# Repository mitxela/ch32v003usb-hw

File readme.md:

# CH32V003 USB dev board

This is a simple and tiny USB dev board for the CH32V003 using CNLohr's ch32v003fun and rv003usb.

2 layer board, 0.8mm thickness.

The 1.5K resistor can be connected either to D5 or to VDD (not both). The series resistors on the underside are optional, cut the traces under them if you want to fit them.

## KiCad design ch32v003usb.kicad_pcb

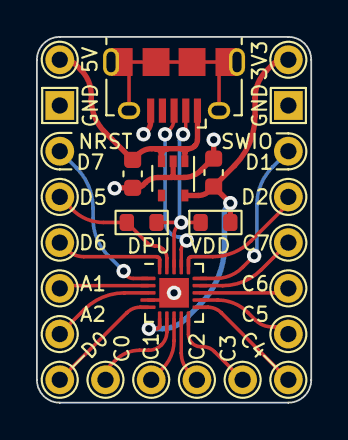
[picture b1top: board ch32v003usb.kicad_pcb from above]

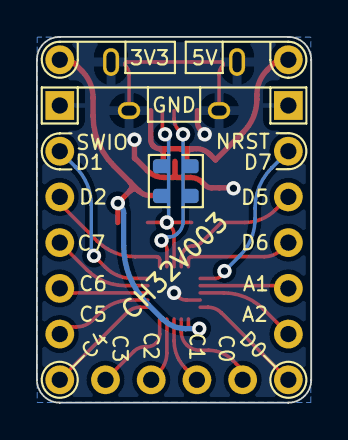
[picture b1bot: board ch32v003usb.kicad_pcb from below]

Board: 2 copper layers, 15.2 x 20.3 mm, 29 parts (2 on the bottom side), 21 nets.

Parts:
C1, C2: 1u; C_0603_1608Metric
J1: USB_B_Micro; USB_Micro-B_Amphenol_10118194_Horizontal
R1, R2: 1K5; R_0603_1608Metric
R3, R4: 33R; R_0603_1608Metric
TP1: C5; TestPoint_THTPad_D1.5mm_Drill0.7mm
TP2: D6; TestPoint_THTPad_D1.5mm_Drill0.7mm
TP3: A2; TestPoint_THTPad_D1.5mm_Drill0.7mm
TP4: D0; TestPoint_THTPad_D1.5mm_Drill0.7mm
TP5: C1; TestPoint_THTPad_D1.5mm_Drill0.7mm
TP6: 3V3; TestPoint_THTPad_D1.5mm_Drill0.7mm
TP7: C2; TestPoint_THTPad_D1.5mm_Drill0.7mm
TP8: C0; TestPoint_THTPad_D1.5mm_Drill0.7mm
TP9: C3; TestPoint_THTPad_D1.5mm_Drill0.7mm
TP10: C4; TestPoint_THTPad_D1.5mm_Drill0.7mm
TP11: C6; TestPoint_THTPad_D1.5mm_Drill0.7mm
TP12: D7; TestPoint_THTPad_D1.5mm_Drill0.7mm
TP13: C7; TestPoint_THTPad_D1.5mm_Drill0.7mm
TP14: A1; TestPoint_THTPad_D1.5mm_Drill0.7mm
TP15: D1; TestPoint_THTPad_D1.5mm_Drill0.7mm
TP16, TP20: GND; TestPoint_THTPad_1.5x1.5mm_Drill0.7mm
TP17: D2; TestPoint_THTPad_D1.5mm_Drill0.7mm
TP18: 5V; TestPoint_THTPad_D1.5mm_Drill0.7mm
TP19: D5; TestPoint_THTPad_D1.5mm_Drill0.7mm
U1: CH32V003F4U6; QFN-20-1EP_3x3mm_P0.4mm_EP1.65x1.65mm
U2: MIC5365-3.3YC5; SOT-353_SC-70-5

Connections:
/DPU: R1.2, TP19.1, U1.19 (PD5)
/USB_D+: J1.3 (D+), R4.1, R4.2, U1.17 (PD3)
/USB_D-: J1.2 (D-), R1.1, R2.1, R3.1, R3.2, U1.18 (PD4)
GND: C1.2, C2.2, J1.5 (GND), J1.6 (Shield), TP16.1, TP20.1, U1.4 (VSS), U1.21 (PAD), U2.2 (GND)
unnamed: C2.1, J1.1 (VBUS), TP18.1, U2.1 (VIN), U2.3 (EN)
unnamed: TP14.1, U1.2 (PA1)
unnamed: TP3.1, U1.3 (PA2)
unnamed: TP8.1, U1.7 (PC0)
unnamed: TP5.1, U1.8 (PC1)
unnamed: TP7.1, U1.9 (PC2)
unnamed: TP9.1, U1.10 (PC3)
unnamed: TP10.1, U1.11 (PC4)
unnamed: TP1.1, U1.12 (PC5)
unnamed: TP11.1, U1.13 (PC6)
unnamed: TP13.1, U1.14 (PC7)
unnamed: TP4.1, U1.5 (PD0)
unnamed: TP15.1, U1.15 (PD1/SWIO)
unnamed: TP17.1, U1.16 (PD2)
unnamed: TP2.1, U1.20 (PD6)
unnamed: TP12.1, U1.1 (PD7)
VDD: C1.1, R2.2, TP6.1, U1.6 (VDD), U2.5 (VOUT)

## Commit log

2023-11-10 routing about done
2023-11-10 ground plane
2023-11-10 Silkscreen updates
2023-11-13 rounding
2023-12-14 Enlarge plated holes
2023-12-15 add readme
